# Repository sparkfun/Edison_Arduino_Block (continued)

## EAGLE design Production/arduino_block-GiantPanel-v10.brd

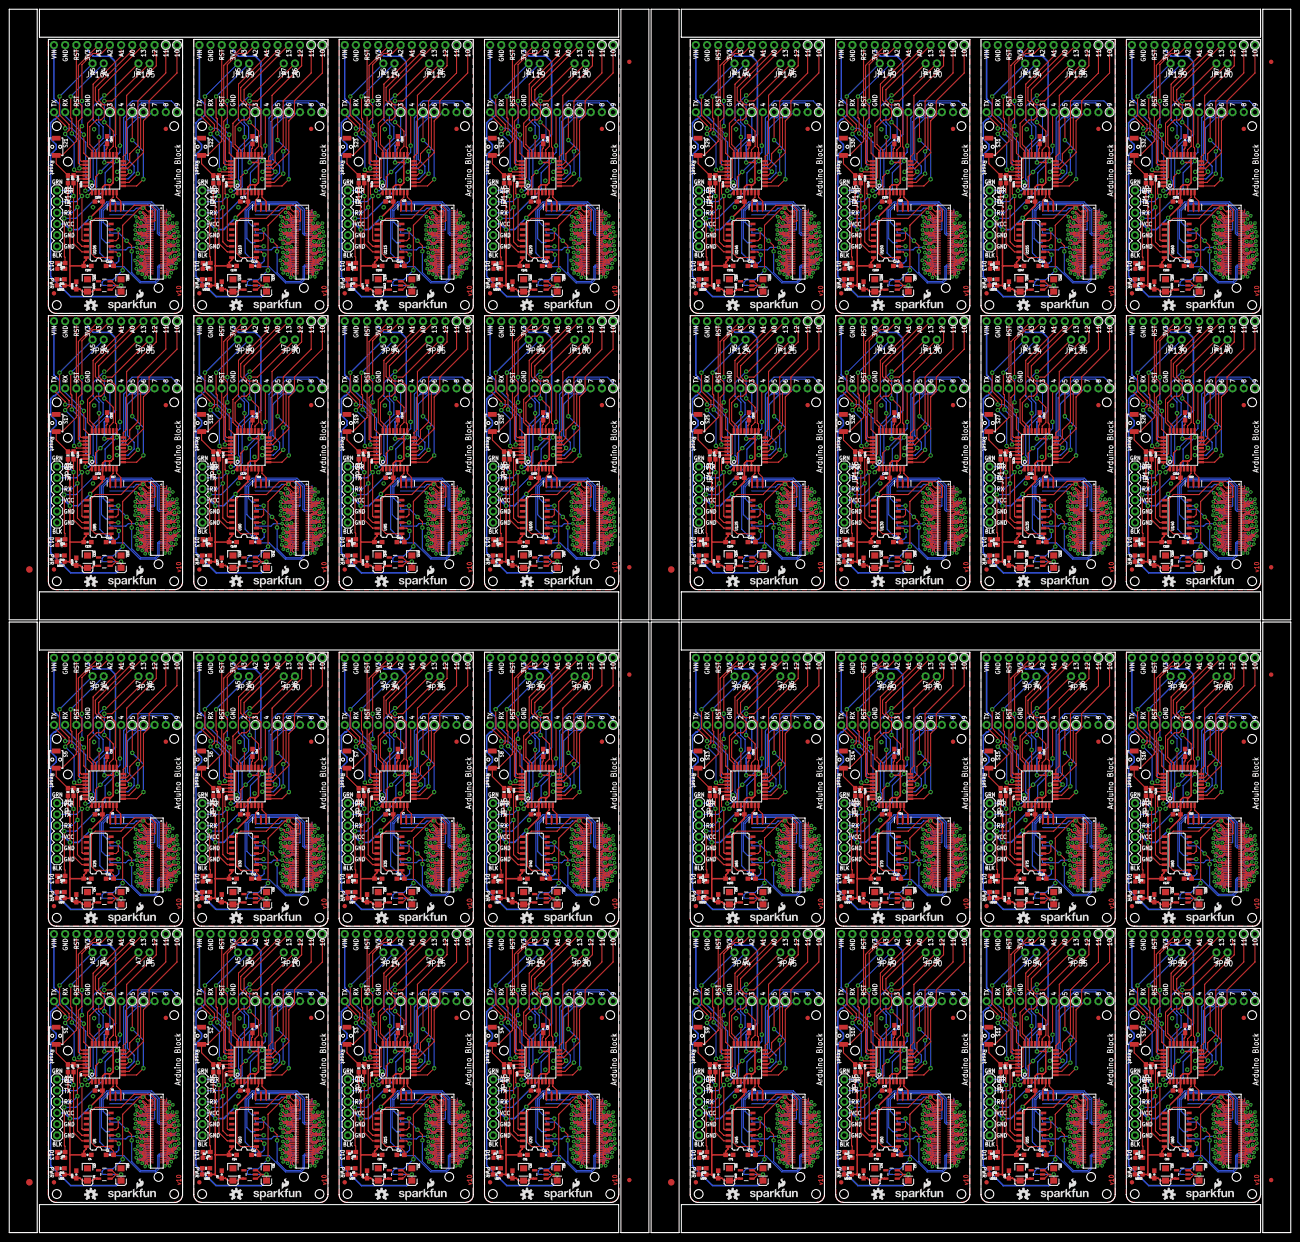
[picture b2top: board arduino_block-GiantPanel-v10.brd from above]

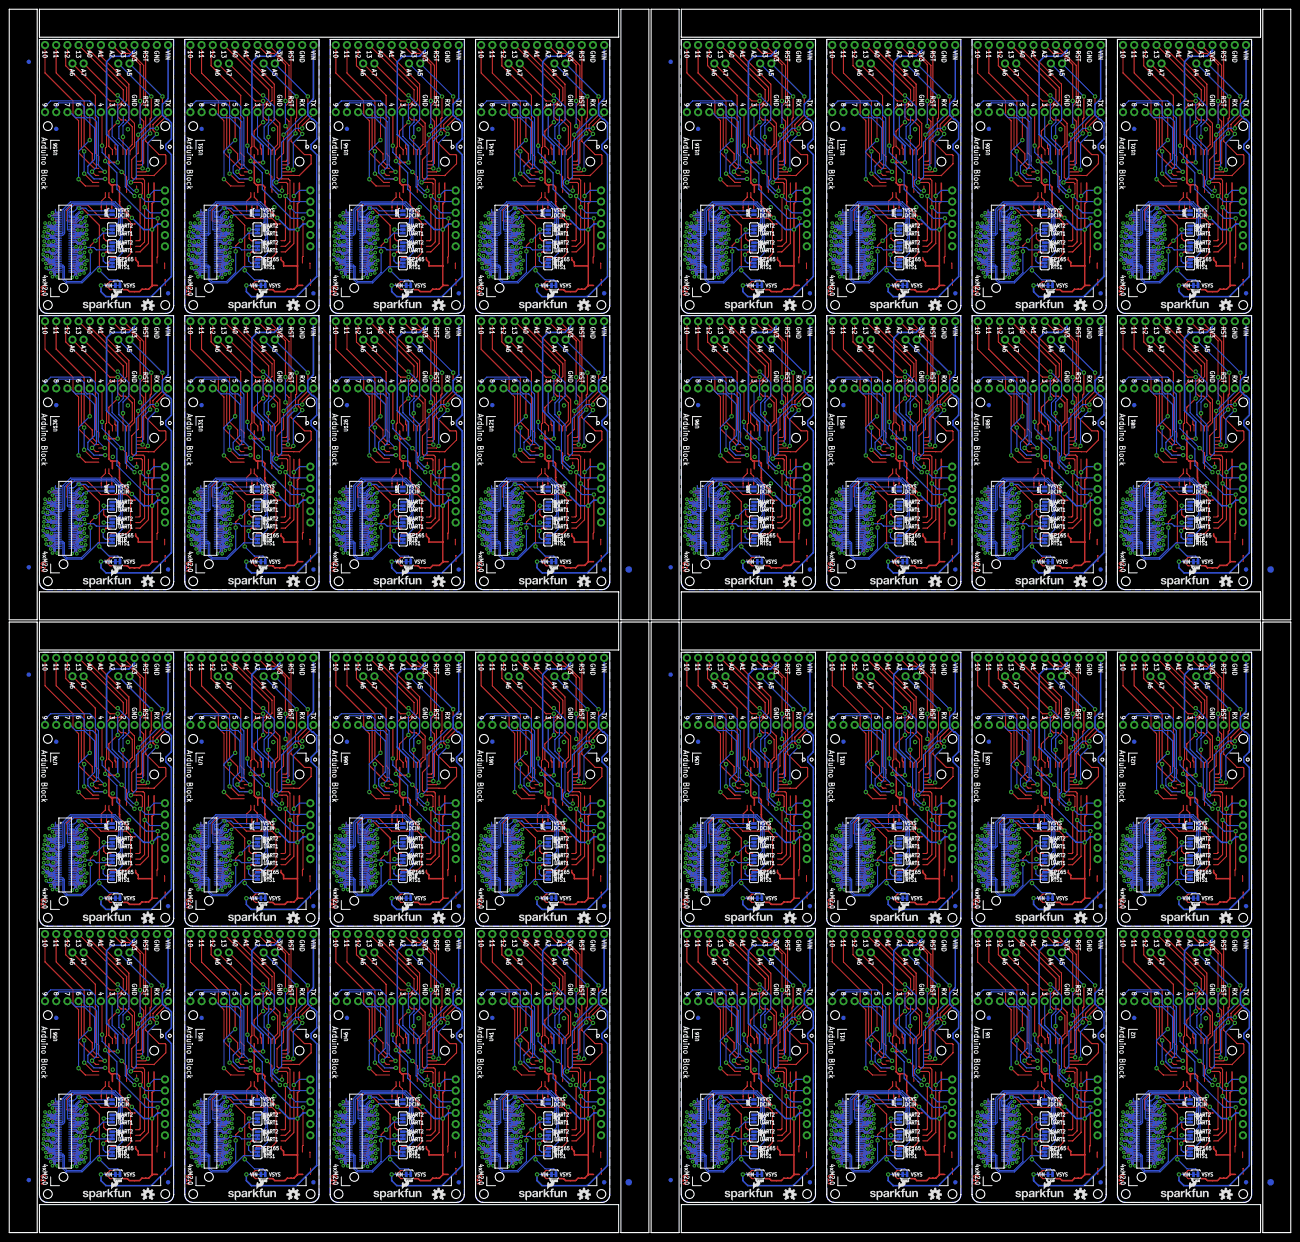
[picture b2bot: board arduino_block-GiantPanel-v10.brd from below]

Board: 2 copper layers, 291.1 x 277.9 mm, 1240 parts (364 on the bottom side), 2944 nets.

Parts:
C1, C2, C3, C4, C5, C6, C8, C9, C10, C12, C14, C15, C16, C18, C20, C22, C23, C24, C25, C27, C28, C30, C31, C32, C33, C35, C36, C38, C39, C40, C41, C43, C44, C46, C47, C48, C49, C51, C52, C54, C55, C56, C57, C59, C60, C62, C63, C64, C65, C67, C68, C70, C71, C72, C73, C75, C76, C78, C79, C80, C81, C83, C84, C86, C87, C88, C89, C91, C92, C94, C95, C96, C97, C99, C100, C102, C103, C104, C105, C107, C108, C110, C111, C112, C113, C115, C116, C118, C119, C120, C121, C123, C124, C126, C127, C128, C129, C131, C132, C134, C135, C136, C137, C139, C140, C142, C143, C144, C145, C147, C148, C150, C151, C152, C153, C155, C156, C158, C159, C160, C161, C163, C164, C166, C167, C168, C169, C171, C172, C174, C175, C176, C177, C179, C180, C182, C183, C184, C185, C187, C188, C190, C191, C192, C193, C195, C196, C198, C199, C200, C201, C203, C204, C206, C207, C208, C209, C211, C212, C214, C215, C216, C217, C219, C220, C222, C223, C224, C225, C227, C228, C230, C231, C232, C233, C235, C236, C238, C239, C240, C241, C243, C244, C246, C247, C248, C249, C251, C252, C254, C255, C256: 0.1uF; 0603-CAP
C7, C11, C13, C17, C19, C21, C26, C29, C34, C37, C42, C45, C50, C53, C58, C61, C66, C69, C74, C77, C82, C85, C90, C93, C98, C101, C106, C109, C114, C117, C122, C125, C130, C133, C138, C141, C146, C149, C154, C157, C162, C165, C170, C173, C178, C181, C186, C189, C194, C197, C202, C205, C210, C213, C218, C221, C226, C229, C234, C237, C242, C245, C250, C253: 10uF; EIA3216
D1, D2, D3, D4, D5, D6, D7, D8, D9, D10, D11, D12, D13, D14, D15, D16, D17, D18, D19, D20, D21, D22, D23, D24, D25, D26, D27, D28, D29, D30, D31, D32: Green; 0603-LED-ALT1
E$1, E$2, E$9, E$10, E$15, E$16, E$21, E$22: FIDUCIAL-1.5X3
E$3, E$4, E$5, E$6, E$7, E$8, E$11, E$12, E$13, E$14, E$17, E$18, E$19, E$20, E$23, E$24: FIDUCIAL-1X2
FID1, FID2, FID3, FID4, FID5, FID6, FID7, FID8, FID9, FID10, FID11, FID12, FID13, FID14, FID15, FID16, FID17, FID18, FID19, FID20, FID21, FID22, FID23, FID24, FID25, FID26, FID27, FID28, FID29, FID30, FID31, FID32, FID33, FID34, FID35, FID36, FID37, FID38, FID39, FID40, FID41, FID42, FID43, FID44, FID45, FID46, FID47, FID48, FID49, FID50, FID51, FID52, FID53, FID54, FID55, FID56, FID57, FID58, FID59, FID60, FID61, FID62, FID63, FID64, FID65, FID66, FID67, FID68, FID69, FID70, FID71, FID72, FID73, FID74, FID75, FID76, FID77, FID78, FID79, FID80, FID81, FID82, FID83, FID84, FID85, FID86, FID87, FID88, FID89, FID90, FID91, FID92, FID93, FID94, FID95, FID96, FID97, FID98, FID99, FID100, FID101, FID102, FID103, FID104, FID105, FID106, FID107, FID108, FID109, FID110, FID111, FID112, FID113, FID114, FID115, FID116, FID117, FID118, FID119, FID120, FID121, FID122, FID123, FID124, FID125, FID126, FID127, FID128: FIDUCIAL1X2; FIDUCIAL-1X2
JP1, JP6, JP11, JP16, JP21, JP26, JP31, JP36, JP41, JP46, JP51, JP56, JP61, JP66, JP71, JP76, JP81, JP86, JP91, JP96, JP101, JP106, JP111, JP116, JP121, JP126, JP131, JP136, JP141, JP146, JP151, JP156: FTDI Basic; 1X06
JP2, JP3, JP7, JP8, JP12, JP13, JP17, JP18, JP22, JP23, JP27, JP28, JP32, JP33, JP37, JP38, JP42, JP43, JP47, JP48, JP52, JP53, JP57, JP58, JP62, JP63, JP67, JP68, JP72, JP73, JP77, JP78, JP82, JP83, JP87, JP88, JP92, JP93, JP97, JP98, JP102, JP103, JP107, JP108, JP112, JP113, JP117, JP118, JP122, JP123, JP127, JP128, JP132, JP133, JP137, JP138, JP142, JP143, JP147, JP148, JP152, JP153, JP157, JP158: M12NO_SILK; 1X12_NO_SILK
JP4, JP5, JP9, JP10, JP14, JP15, JP19, JP20, JP24, JP25, JP29, JP30, JP34, JP35, JP39, JP40, JP44, JP45, JP49, JP50, JP54, JP55, JP59, JP60, JP64, JP65, JP69, JP70, JP74, JP75, JP79, JP80, JP84, JP85, JP89, JP90, JP94, JP95, JP99, JP100, JP104, JP105, JP109, JP110, JP114, JP115, JP119, JP120, JP124, JP125, JP129, JP130, JP134, JP135, JP139, JP140, JP144, JP145, JP149, JP150, JP154, JP155, JP159, JP160: M021X02_NO_SILK; 1X02_NO_SILK
LED1, LED2, LED3, LED4, LED5, LED6, LED7, LED8, LED9, LED10, LED11, LED12, LED13, LED14, LED15, LED16, LED17, LED18, LED19, LED20, LED21, LED22, LED23, LED24, LED25, LED26, LED27, LED28, LED29, LED30, LED31, LED32: Red; 0603-LED-ALT1
LOGO1, LOGO2, LOGO5, LOGO7, LOGO9, LOGO11, LOGO13, LOGO15, LOGO17, LOGO19, LOGO21, LOGO23, LOGO25, LOGO27, LOGO29, LOGO31, LOGO33, LOGO35, LOGO37, LOGO39, LOGO41, LOGO43, LOGO45, LOGO47, LOGO49, LOGO51, LOGO53, LOGO55, LOGO57, LOGO59, LOGO61, LOGO63, LOGO65, LOGO67, LOGO69, LOGO71, LOGO73, LOGO75, LOGO77, LOGO79, LOGO81, LOGO83, LOGO85, LOGO87, LOGO89, LOGO91, LOGO93, LOGO95, LOGO97, LOGO99, LOGO101, LOGO103, LOGO105, LOGO107, LOGO109, LOGO111, LOGO113, LOGO115, LOGO117, LOGO119, LOGO121, LOGO123, LOGO125, LOGO127: OSHW-LOGOS; OSHW-LOGO-S
LOGO3, LOGO4, LOGO6, LOGO8, LOGO10, LOGO12, LOGO14, LOGO16, LOGO18, LOGO20, LOGO22, LOGO24, LOGO26, LOGO28, LOGO30, LOGO32, LOGO34, LOGO36, LOGO38, LOGO40, LOGO42, LOGO44, LOGO46, LOGO48, LOGO50, LOGO52, LOGO54, LOGO56, LOGO58, LOGO60, LOGO62, LOGO64, LOGO66, LOGO68, LOGO70, LOGO72, LOGO74, LOGO76, LOGO78, LOGO80, LOGO82, LOGO84, LOGO86, LOGO88, LOGO90, LOGO92, LOGO94, LOGO96, LOGO98, LOGO100, LOGO102, LOGO104, LOGO106, LOGO108, LOGO110, LOGO112, LOGO114, LOGO116, LOGO118, LOGO120, LOGO122, LOGO124, LOGO126, LOGO128: SFE_LOGO_NAME_FLAME.1_INCH; SFE_LOGO_NAME_FLAME_.1
R1, R2, R3, R5, R7, R9, R10, R11, R13, R14, R16, R17, R19, R20, R22, R23, R25, R26, R28, R29, R31, R32, R34, R35, R37, R38, R40, R41, R43, R44, R46, R47, R49, R50, R52, R53, R55, R56, R58, R59, R61, R62, R64, R65, R67, R68, R70, R71, R73, R74, R76, R77, R79, R80, R82, R83, R85, R86, R88, R89, R91, R92, R94, R95: 10K; 0603-RES
R4, R6, R8, R12, R15, R18, R21, R24, R27, R30, R33, R36, R39, R42, R45, R48, R51, R54, R57, R60, R63, R66, R69, R72, R75, R78, R81, R84, R87, R90, R93, R96: 330; 0603-RES
S1, S2, S3, S4, S5, S6, S7, S8, S9, S10, S11, S12, S13, S14, S15, S16, S17, S18, S19, S20, S21, S22, S23, S24, S25, S26, S27, S28, S29, S30, S31, S32: RESET; TACTILE_SWITCH-SMD-RIGHT-ANGLE
SJ1, SJ3, SJ6, SJ9, SJ11, SJ14, SJ16, SJ19, SJ21, SJ24, SJ26, SJ29, SJ31, SJ34, SJ36, SJ39, SJ41, SJ44, SJ46, SJ49, SJ51, SJ54, SJ56, SJ59, SJ61, SJ64, SJ66, SJ69, SJ71, SJ74, SJ76, SJ79, SJ81, SJ84, SJ86, SJ89, SJ91, SJ94, SJ96, SJ99, SJ101, SJ104, SJ106, SJ109, SJ111, SJ114, SJ116, SJ119, SJ121, SJ124, SJ126, SJ129, SJ131, SJ134, SJ136, SJ139, SJ141, SJ144, SJ146, SJ149, SJ151, SJ154, SJ156, SJ159: TX; PAD-JUMPER-3-2OF3_NC_BY_TRACE_YES_SILK_FULL_BOX
SJ2, SJ7, SJ12, SJ17, SJ22, SJ27, SJ32, SJ37, SJ42, SJ47, SJ52, SJ57, SJ62, SJ67, SJ72, SJ77, SJ82, SJ87, SJ92, SJ97, SJ102, SJ107, SJ112, SJ117, SJ122, SJ127, SJ132, SJ137, SJ142, SJ147, SJ152, SJ157: RX; PAD-JUMPER-3-2OF3_NC_BY_TRACE_YES_SILK_FULL_BOX
SJ4, SJ8, SJ13, SJ18, SJ23, SJ28, SJ33, SJ38, SJ43, SJ48, SJ53, SJ58, SJ63, SJ68, SJ73, SJ78, SJ83, SJ88, SJ93, SJ98, SJ103, SJ108, SJ113, SJ118, SJ123, SJ128, SJ133, SJ138, SJ143, SJ148, SJ153, SJ158: VIN; PAD-JUMPER-2-NC_BY_TRACE_YES_SILK
SJ5, SJ10, SJ15, SJ20, SJ25, SJ30, SJ35, SJ40, SJ45, SJ50, SJ55, SJ60, SJ65, SJ70, SJ75, SJ80, SJ85, SJ90, SJ95, SJ100, SJ105, SJ110, SJ115, SJ120, SJ125, SJ130, SJ135, SJ140, SJ145, SJ150, SJ155, SJ160: DCIN; PAD-JUMPER-2-NO_YES_SILK
U1, U8, U13, U18, U23, U28, U33, U38, U43, U48, U53, U58, U63, U68, U73, U78, U83, U88, U93, U98, U103, U108, U113, U118, U123, U128, U133, U138, U143, U148, U153, U158: MIC5205-3.3V (150mA); SOT23-5
U2, U6, U11, U16, U21, U26, U31, U36, U41, U46, U51, U56, U61, U66, U71, U76, U81, U86, U91, U96, U101, U106, U111, U116, U121, U126, U131, U136, U141, U146, U151, U156: EDISON_CONNECTOR_FULLMOUNTING_HOLES; EDISON_DAUGHTER
U3, U7, U12, U17, U22, U27, U32, U37, U42, U47, U52, U57, U62, U67, U72, U77, U82, U87, U92, U97, U102, U107, U112, U117, U122, U127, U132, U137, U142, U147, U152, U157: EDISON_CONNECTOR_FULLHEADER; DF40C-70DP-0.4(51)
U4, U9, U14, U19, U24, U29, U34, U39, U44, U49, U54, U59, U64, U69, U74, U79, U84, U89, U94, U99, U104, U109, U114, U119, U124, U129, U134, U139, U144, U149, U154, U159: ATMEGA328; TQFP32-08
U5, U10, U15, U20, U25, U30, U35, U40, U45, U50, U55, U60, U65, U70, U75, U80, U85, U90, U95, U100, U105, U110, U115, U120, U125, U130, U135, U140, U145, U150, U155, U160: SO14
Y1, Y2, Y3, Y4, Y5, Y6, Y7, Y8, Y9, Y10, Y11, Y12, Y13, Y14, Y15, Y16, Y17, Y18, Y19, Y20, Y21, Y22, Y23, Y24, Y25, Y26, Y27, Y28, Y29, Y30, Y31, Y32: 8MHZ; RESONATOR-SMD

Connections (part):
1.8V: C5.2, U2.12, U3.12, U5.1, U5.8
1.8V1: C15.2, U6.12, U7.12, U10.1, U10.8
1.8V2: C24.2, U11.12, U12.12, U15.1, U15.8
1.8V3: C32.2, U16.12, U17.12, U20.1, U20.8
1.8V4: C40.2, U21.12, U22.12, U25.1, U25.8
1.8V5: C48.2, U26.12, U27.12, U30.1, U30.8
1.8V6: C56.2, U31.12, U32.12, U35.1, U35.8
1.8V7: C64.2, U36.12, U37.12, U40.1, U40.8
1.8V8: C72.2, U41.12, U42.12, U45.1, U45.8
1.8V9: C80.2, U46.12, U47.12, U50.1, U50.8
1.8V10: C88.2, U51.12, U52.12, U55.1, U55.8
1.8V11: C96.2, U56.12, U57.12, U60.1, U60.8
1.8V12: C104.2, U61.12, U62.12, U65.1, U65.8
1.8V13: C112.2, U66.12, U67.12, U70.1, U70.8
1.8V14: C120.2, U71.12, U72.12, U75.1, U75.8
1.8V15: C128.2, U76.12, U77.12, U80.1, U80.8
1.8V16: C136.2, U81.12, U82.12, U85.1, U85.8
1.8V17: C144.2, U86.12, U87.12, U90.1, U90.8
1.8V18: C152.2, U91.12, U92.12, U95.1, U95.8
1.8V19: C160.2, U96.12, U97.12, U100.1, U100.8
1.8V20: C168.2, U101.12, U102.12, U105.1, U105.8
1.8V21: C176.2, U106.12, U107.12, U110.1, U110.8
1.8V22: C184.2, U111.12, U112.12, U115.1, U115.8
1.8V23: C192.2, U116.12, U117.12, U120.1, U120.8
1.8V24: C200.2, U121.12, U122.12, U125.1, U125.8
1.8V25: C208.2, U126.12, U127.12, U130.1, U130.8
1.8V26: C216.2, U131.12, U132.12, U135.1, U135.8
1.8V27: C224.2, U136.12, U137.12, U140.1, U140.8
1.8V28: C232.2, U141.12, U142.12, U145.1, U145.8
1.8V29: C240.2, U146.12, U147.12, U150.1, U150.8
1.8V30: C248.2, U151.12, U152.12, U155.1, U155.8
1.8V31: C256.2, U156.12, U157.12, U160.1, U160.8
3.3V: U2.8, U2.10, U3.8, U3.10
3.3V1: U6.8, U6.10, U7.8, U7.10
3.3V2: U11.8, U11.10, U12.8, U12.10
3.3V3: U16.8, U16.10, U17.8, U17.10
3.3V4: U21.8, U21.10, U22.8, U22.10
3.3V5: U26.8, U26.10, U27.8, U27.10
3.3V6: U31.8, U31.10, U32.8, U32.10
3.3V7: U36.8, U36.10, U37.8, U37.10
3.3V8: U41.8, U41.10, U42.8, U42.10
3.3V9: U46.8, U46.10, U47.8, U47.10
3.3V10: U51.8, U51.10, U52.8, U52.10
3.3V11: U56.8, U56.10, U57.8, U57.10
3.3V12: U61.8, U61.10, U62.8, U62.10
3.3V13: U66.8, U66.10, U67.8, U67.10
3.3V14: U71.8, U71.10, U72.8, U72.10
3.3V15: U76.8, U76.10, U77.8, U77.10
3.3V16: U81.8, U81.10, U82.8, U82.10
3.3V17: U86.8, U86.10, U87.8, U87.10
3.3V18: U91.8, U91.10, U92.8, U92.10
3.3V19: U96.8, U96.10, U97.8, U97.10
3.3V20: U101.8, U101.10, U102.8, U102.10
3.3V21: U106.8, U106.10, U107.8, U107.10
3.3V22: U111.8, U111.10, U112.8, U112.10
3.3V23: U116.8, U116.10, U117.8, U117.10
3.3V24: U121.8, U121.10, U122.8, U122.10
3.3V25: U126.8, U126.10, U127.8, U127.10
3.3V26: U131.8, U131.10, U132.8, U132.10
3.3V27: U136.8, U136.10, U137.8, U137.10
3.3V28: U141.8, U141.10, U142.8, U142.10
3.3V29: U146.8, U146.10, U147.8, U147.10
3.3V30: U151.8, U151.10, U152.8, U152.10
3.3V31: U156.8, U156.10, U157.8, U157.10
A0: JP2.8, U4.23
A1: JP2.7, U4.24
A2: JP2.6, U4.25
A3: JP2.5, U4.26
A4: JP4.1, U4.27
A5: JP4.2, U4.28
A6: JP5.1, U4.19
A7: JP5.2, U4.22
A8: JP9.2, U9.28
A9: JP9.1, U9.27
A10: JP7.5, U9.26
A11: JP7.6, U9.25
A12: JP7.7, U9.24
A13: JP7.8, U9.23
A14: JP10.1, U9.19
A15: JP10.2, U9.22
A16: JP14.2, U14.28
A17: JP14.1, U14.27
A18: JP12.5, U14.26
A19: JP12.6, U14.25
A20: JP12.7, U14.24
A21: JP12.8, U14.23
A22: JP15.1, U14.19
A23: JP15.2, U14.22
A24: JP19.2, U19.28
A25: JP19.1, U19.27
A26: JP17.5, U19.26
A27: JP17.6, U19.25
A28: JP17.7, U19.24
A29: JP17.8, U19.23
A30: JP20.1, U19.19
A31: JP20.2, U19.22
A32: JP24.2, U24.28
A33: JP24.1, U24.27
A34: JP22.5, U24.26
A35: JP22.6, U24.25
A36: JP22.7, U24.24
A37: JP22.8, U24.23
A38: JP25.1, U24.19
A39: JP25.2, U24.22
A40: JP29.2, U29.28
A41: JP29.1, U29.27
A42: JP27.5, U29.26
A43: JP27.6, U29.25
A44: JP27.7, U29.24
A45: JP27.8, U29.23
A46: JP30.1, U29.19
A47: JP30.2, U29.22
A48: JP34.2, U34.28
A49: JP34.1, U34.27
A50: JP32.5, U34.26
A51: JP32.6, U34.25
A52: JP32.7, U34.24
A53: JP32.8, U34.23
A54: JP35.1, U34.19
A55: JP35.2, U34.22
A56: JP39.2, U39.28
A57: JP39.1, U39.27
A58: JP37.5, U39.26
A59: JP37.6, U39.25
A60: JP37.7, U39.24
A61: JP37.8, U39.23
A62: JP40.1, U39.19
A63: JP40.2, U39.22
A64: JP44.2, U44.28
A65: JP44.1, U44.27
A66: JP42.5, U44.26
A67: JP42.6, U44.25
A68: JP42.7, U44.24
A69: JP42.8, U44.23
A70: JP45.1, U44.19
A71: JP45.2, U44.22
A72: JP49.2, U49.28
A73: JP49.1, U49.27
A74: JP47.5, U49.26
A75: JP47.6, U49.25
A76: JP47.7, U49.24
A77: JP47.8, U49.23
A78: JP50.1, U49.19
A79: JP50.2, U49.22
A80: JP54.2, U54.28
A81: JP54.1, U54.27
A82: JP52.5, U54.26
A83: JP52.6, U54.25
A84: JP52.7, U54.24
A85: JP52.8, U54.23
A86: JP55.1, U54.19
A87: JP55.2, U54.22
A88: JP59.2, U59.28
A89: JP59.1, U59.27
A90: JP57.5, U59.26
A91: JP57.6, U59.25
A92: JP57.7, U59.24
A93: JP57.8, U59.23
A94: JP60.1, U59.19
A95: JP60.2, U59.22
A96: JP64.2, U64.28
A97: JP64.1, U64.27
A98: JP62.5, U64.26
A99: JP62.6, U64.25
A100: JP62.7, U64.24
A101: JP62.8, U64.23
A102: JP65.1, U64.19
A103: JP65.2, U64.22
A104: JP69.2, U69.28
A105: JP69.1, U69.27
A106: JP67.5, U69.26
A107: JP67.6, U69.25
A108: JP67.7, U69.24
A109: JP67.8, U69.23
A110: JP70.1, U69.19
A111: JP70.2, U69.22
A112: JP74.2, U74.28
A113: JP74.1, U74.27
A114: JP72.5, U74.26
A115: JP72.6, U74.25
A116: JP72.7, U74.24
A117: JP72.8, U74.23
A118: JP75.1, U74.19
A119: JP75.2, U74.22
A120: JP79.2, U79.28
A121: JP79.1, U79.27
A122: JP77.5, U79.26
A123: JP77.6, U79.25
A124: JP77.7, U79.24
A125: JP77.8, U79.23
A126: JP80.1, U79.19
A127: JP80.2, U79.22
A128: JP84.2, U84.28
A129: JP84.1, U84.27
A130: JP82.5, U84.26
A131: JP82.6, U84.25
A132: JP82.7, U84.24
A133: JP82.8, U84.23
A134: JP85.1, U84.19
A135: JP85.2, U84.22
A136: JP89.2, U89.28
A137: JP89.1, U89.27
A138: JP87.5, U89.26
A139: JP87.6, U89.25
A140: JP87.7, U89.24
A141: JP87.8, U89.23
A142: JP90.1, U89.19
A143: JP90.2, U89.22
A144: JP94.2, U94.28
A145: JP94.1, U94.27
A146: JP92.5, U94.26
A147: JP92.6, U94.25
A148: JP92.7, U94.24
A149: JP92.8, U94.23
A150: JP95.1, U94.19
A151: JP95.2, U94.22
A152: JP99.2, U99.28
A153: JP99.1, U99.27
A154: JP97.5, U99.26
A155: JP97.6, U99.25
A156: JP97.7, U99.24
A157: JP97.8, U99.23
A158: JP100.1, U99.19
A159: JP100.2, U99.22
A160: JP104.2, U104.28
A161: JP104.1, U104.27
A162: JP102.5, U104.26
A163: JP102.6, U104.25
A164: JP102.7, U104.24
A165: JP102.8, U104.23
A166: JP105.1, U104.19
A167: JP105.2, U104.22
A168: JP109.2, U109.28
A169: JP109.1, U109.27
A170: JP107.5, U109.26
A171: JP107.6, U109.25
A172: JP107.7, U109.24
A173: JP107.8, U109.23
A174: JP110.1, U109.19
A175: JP110.2, U109.22
A176: JP114.2, U114.28
A177: JP114.1, U114.27
A178: JP112.5, U114.26
A179: JP112.6, U114.25
A180: JP112.7, U114.24
A181: JP112.8, U114.23
A182: JP115.1, U114.19
A183: JP115.2, U114.22
A184: JP119.2, U119.28
A185: JP119.1, U119.27
A186: JP117.5, U119.26
A187: JP117.6, U119.25
A188: JP117.7, U119.24
A189: JP117.8, U119.23
A190: JP120.1, U119.19
A191: JP120.2, U119.22
A192: JP124.2, U124.28
A193: JP124.1, U124.27
A194: JP122.5, U124.26
A195: JP122.6, U124.25
A196: JP122.7, U124.24
A197: JP122.8, U124.23
A198: JP125.1, U124.19
A199: JP125.2, U124.22
A200: JP129.2, U129.28
A201: JP129.1, U129.27
A202: JP127.5, U129.26
A203: JP127.6, U129.25
A204: JP127.7, U129.24
A205: JP127.8, U129.23
A206: JP130.1, U129.19
A207: JP130.2, U129.22
A208: JP134.2, U134.28
A209: JP134.1, U134.27
A210: JP132.5, U134.26
A211: JP132.6, U134.25
A212: JP132.7, U134.24
A213: JP132.8, U134.23
A214: JP135.1, U134.19
A215: JP135.2, U134.22
A216: JP139.2, U139.28
A217: JP139.1, U139.27
A218: JP137.5, U139.26
A219: JP137.6, U139.25
A220: JP137.7, U139.24
A221: JP137.8, U139.23
A222: JP140.1, U139.19
A223: JP140.2, U139.22
A224: JP144.2, U144.28
A225: JP144.1, U144.27
A226: JP142.5, U144.26
A227: JP142.6, U144.25
A228: JP142.7, U144.24
A229: JP142.8, U144.23
A230: JP145.1, U144.19
A231: JP145.2, U144.22
A232: JP149.2, U149.28
A233: JP149.1, U149.27
A234: JP147.5, U149.26
A235: JP147.6, U149.25
A236: JP147.7, U149.24
A237: JP147.8, U149.23
A238: JP150.1, U149.19
A239: JP150.2, U149.22
A240: JP154.2, U154.28
A241: JP154.1, U154.27
A242: JP152.5, U154.26
A243: JP152.6, U154.25
A244: JP152.7, U154.24
A245: JP152.8, U154.23
A246: JP155.1, U154.19
A247: JP155.2, U154.22
A248: JP159.2, U159.28
A249: JP159.1, U159.27
A250: JP157.5, U159.26
A251: JP157.6, U159.25
A252: JP157.7, U159.24
A253: JP157.8, U159.23
A254: JP160.1, U159.19
A255: JP160.2, U159.22
ARD_DTR: C2.2, JP1.1, U5.13
ARD_DTR1: C12.2, JP6.1, U10.13
ARD_DTR2: C22.2, JP11.1, U15.13
ARD_DTR3: C30.2, JP16.1, U20.13
ARD_DTR4: C38.2, JP21.1, U25.13
ARD_DTR5: C46.2, JP26.1, U30.13
ARD_DTR6: C54.2, JP31.1, U35.13
ARD_DTR7: C62.2, JP36.1, U40.13
ARD_DTR8: C70.2, JP41.1, U45.13
ARD_DTR9: C78.2, JP46.1, U50.13
ARD_DTR10: C86.2, JP51.1, U55.13
ARD_DTR11: C94.2, JP56.1, U60.13
ARD_DTR12: C102.2, JP61.1, U65.13
ARD_DTR13: C110.2, JP66.1, U70.13
ARD_DTR14: C118.2, JP71.1, U75.13
ARD_DTR15: C126.2, JP76.1, U80.13
ARD_DTR16: C134.2, JP81.1, U85.13
ARD_DTR17: C142.2, JP86.1, U90.13
ARD_DTR18: C150.2, JP91.1, U95.13
ARD_DTR19: C158.2, JP96.1, U100.13
ARD_DTR20: C166.2, JP101.1, U105.13
ARD_DTR21: C174.2, JP106.1, U110.13
ARD_DTR22: C182.2, JP111.1, U115.13
ARD_DTR23: C190.2, JP116.1, U120.13
ARD_DTR24: C198.2, JP121.1, U125.13
ARD_DTR25: C206.2, JP126.1, U130.13
ARD_DTR26: C214.2, JP131.1, U135.13
ARD_DTR27: C222.2, JP136.1, U140.13
ARD_DTR28: C230.2, JP141.1, U145.13
ARD_DTR29: C238.2, JP146.1, U150.13
ARD_DTR30: C246.2, JP151.1, U155.13
ARD_DTR31: C254.2, JP156.1, U160.13
ARD_RX: JP1.3, JP3.2, U4.30, U5.12
ARD_RX1: JP6.3, JP8.2, U9.30, U10.12
ARD_RX2: JP11.3, JP13.2, U14.30, U15.12
ARD_RX3: JP16.3, JP18.2, U19.30, U20.12
ARD_RX4: JP21.3, JP23.2, U24.30, U25.12
ARD_RX5: JP26.3, JP28.2, U29.30, U30.12
ARD_RX6: JP31.3, JP33.2, U34.30, U35.12
ARD_RX7: JP36.3, JP38.2, U39.30, U40.12
ARD_RX8: JP41.3, JP43.2, U44.30, U45.12
ARD_RX9: JP46.3, JP48.2, U49.30, U50.12
ARD_RX10: JP51.3, JP53.2, U54.30, U55.12
ARD_RX11: JP56.3, JP58.2, U59.30, U60.12
ARD_RX12: JP61.3, JP63.2, U64.30, U65.12
ARD_RX13: JP66.3, JP68.2, U69.30, U70.12
ARD_RX14: JP71.3, JP73.2, U74.30, U75.12
ARD_RX15: JP76.3, JP78.2, U79.30, U80.12
ARD_RX16: JP81.3, JP83.2, U84.30, U85.12
ARD_RX17: JP86.3, JP88.2, U89.30, U90.12
ARD_RX18: JP91.3, JP93.2, U94.30, U95.12
ARD_RX19: JP96.3, JP98.2, U99.30, U100.12
ARD_RX20: JP101.3, JP103.2, U104.30, U105.12
ARD_RX21: JP106.3, JP108.2, U109.30, U110.12
ARD_RX22: JP111.3, JP113.2, U114.30, U115.12
ARD_RX23: JP116.3, JP118.2, U119.30, U120.12
ARD_RX24: JP121.3, JP123.2, U124.30, U125.12
ARD_RX25: JP126.3, JP128.2, U129.30, U130.12
ARD_RX26: JP131.3, JP133.2, U134.30, U135.12
ARD_RX27: JP136.3, JP138.2, U139.30, U140.12
ARD_RX28: JP141.3, JP143.2, U144.30, U145.12
ARD_RX29: JP146.3, JP148.2, U149.30, U150.12
ARD_RX30: JP151.3, JP153.2, U154.30, U155.12
ARD_RX31: JP156.3, JP158.2, U159.30, U160.12
ARD_TX: JP1.2, JP3.1, U4.31, U5.11
ARD_TX1: JP6.2, JP8.1, U9.31, U10.11
ARD_TX2: JP11.2, JP13.1, U14.31, U15.11
ARD_TX3: JP16.2, JP18.1, U19.31, U20.11
ARD_TX4: JP21.2, JP23.1, U24.31, U25.11
ARD_TX5: JP26.2, JP28.1, U29.31, U30.11
ARD_TX6: JP31.2, JP33.1, U34.31, U35.11
ARD_TX7: JP36.2, JP38.1, U39.31, U40.11
ARD_TX8: JP41.2, JP43.1, U44.31, U45.11
ARD_TX9: JP46.2, JP48.1, U49.31, U50.11
ARD_TX10: JP51.2, JP53.1, U54.31, U55.11
ARD_TX11: JP56.2, JP58.1, U59.31, U60.11
ARD_TX12: JP61.2, JP63.1, U64.31, U65.11
ARD_TX13: JP66.2, JP68.1, U69.31, U70.11
ARD_TX14: JP71.2, JP73.1, U74.31, U75.11
ARD_TX15: JP76.2, JP78.1, U79.31, U80.11
ARD_TX16: JP81.2, JP83.1, U84.31, U85.11
ARD_TX17: JP86.2, JP88.1, U89.31, U90.11
ARD_TX18: JP91.2, JP93.1, U94.31, U95.11
ARD_TX19: JP96.2, JP98.1, U99.31, U100.11
ARD_TX20: JP101.2, JP103.1, U104.31, U105.11
ARD_TX21: JP106.2, JP108.1, U109.31, U110.11
ARD_TX22: JP111.2, JP113.1, U114.31, U115.11
ARD_TX23: JP116.2, JP118.1, U119.31, U120.11
ARD_TX24: JP121.2, JP123.1, U124.31, U125.11
ARD_TX25: JP126.2, JP128.1, U129.31, U130.11
ARD_TX26: JP131.2, JP133.1, U134.31, U135.11
ARD_TX27: JP136.2, JP138.1, U139.31, U140.11
ARD_TX28: JP141.2, JP143.1, U144.31, U145.11
ARD_TX29: JP146.2, JP148.1, U149.31, U150.11
ARD_TX30: JP151.2, JP153.1, U154.31, U155.11
ARD_TX31: JP156.2, JP158.1, U159.31, U160.11
AREF: C1.2, U4.20
AREF1: C9.2, U9.20
AREF2: C20.2, U14.20
AREF3: C28.2, U19.20
AREF4: C36.2, U24.20
AREF5: C44.2, U29.20
AREF6: C52.2, U34.20
AREF7: C60.2, U39.20
AREF8: C68.2, U44.20
AREF9: C76.2, U49.20
AREF10: C84.2, U54.20
AREF11: C92.2, U59.20
AREF12: C100.2, U64.20
AREF13: C108.2, U69.20
AREF14: C116.2, U74.20
AREF15: C124.2, U79.20
AREF16: C132.2, U84.20
AREF17: C140.2, U89.20
AREF18: C148.2, U94.20
AREF19: C156.2, U99.20
AREF20: C164.2, U104.20
AREF21: C172.2, U109.20
AREF22: C180.2, U114.20
AREF23: C188.2, U119.20
AREF24: C196.2, U124.20
AREF25: C204.2, U129.20
AREF26: C212.2, U134.20
AREF27: C220.2, U139.20
AREF28: C228.2, U144.20
AREF29: C236.2, U149.20
AREF30: C244.2, U154.20
AREF31: C252.2, U159.20
D1: JP8.12, U9.13
D2: JP3.5, U4.32
D3: JP3.6, U4.1
D4: JP3.7, U4.2
D5: JP3.8, U4.9
D6: JP3.9, U4.10
D7: JP3.10, U4.11
D8: JP3.11, U4.12
D9: JP3.12, U4.13
D10: JP2.12, U4.14
D11: JP8.11, U9.12
D12: JP8.5, U9.32
D13: JP8.6, U9.1
D14: JP8.7, U9.2
D15: JP8.8, U9.9
D16: JP8.9, U9.10
D17: JP8.10, U9.11
D18: JP7.12, U9.14
D19: JP13.12, U14.13
D20: JP13.11, U14.12
D21: JP13.5, U14.32
D22: JP13.6, U14.1
D23: JP13.7, U14.2
D24: JP13.8, U14.9
D25: JP13.9, U14.10
D26: JP13.10, U14.11
D27: JP12.12, U14.14
D28: JP18.12, U19.13
D29: JP18.11, U19.12
D30: JP18.5, U19.32
D31: JP18.6, U19.1
D32: JP18.7, U19.2
D33: JP18.8, U19.9
D34: JP18.9, U19.10
D35: JP18.10, U19.11
D36: JP17.12, U19.14
D37: JP23.12, U24.13
D38: JP23.11, U24.12
D39: JP23.5, U24.32
D40: JP23.6, U24.1
D41: JP23.7, U24.2
D42: JP23.8, U24.9
D43: JP23.9, U24.10
D44: JP23.10, U24.11
D45: JP22.12, U24.14
D46: JP28.12, U29.13
D47: JP28.11, U29.12
D48: JP28.5, U29.32
D49: JP28.6, U29.1
D50: JP28.7, U29.2
D51: JP28.8, U29.9
D52: JP28.9, U29.10
D53: JP28.10, U29.11
D54: JP27.12, U29.14
D55: JP33.12, U34.13
D56: JP33.11, U34.12
D57: JP33.5, U34.32
D58: JP33.6, U34.1
D59: JP33.7, U34.2
D60: JP33.8, U34.9
D61: JP33.9, U34.10
D62: JP33.10, U34.11
D63: JP32.12, U34.14
D64: JP38.12, U39.13
D65: JP38.11, U39.12
D66: JP38.5, U39.32
D67: JP38.6, U39.1
D68: JP38.7, U39.2
D69: JP38.8, U39.9
D70: JP38.9, U39.10
D71: JP38.10, U39.11
D72: JP37.12, U39.14
D73: JP43.12, U44.13
D74: JP43.11, U44.12
D75: JP43.5, U44.32
D76: JP43.6, U44.1
D77: JP43.7, U44.2
D78: JP43.8, U44.9
D79: JP43.9, U44.10
D80: JP43.10, U44.11
D81: JP42.12, U44.14
D82: JP48.12, U49.13
D83: JP48.11, U49.12
D84: JP48.5, U49.32
D85: JP48.6, U49.1
D86: JP48.7, U49.2
D87: JP48.8, U49.9
D88: JP48.9, U49.10
D89: JP48.10, U49.11
D90: JP47.12, U49.14
D91: JP53.12, U54.13
D92: JP53.11, U54.12
D93: JP53.5, U54.32
D94: JP53.6, U54.1
D95: JP53.7, U54.2
D96: JP53.8, U54.9
D97: JP53.9, U54.10
D98: JP53.10, U54.11
D99: JP52.12, U54.14
D100: JP58.12, U59.13
D101: JP58.11, U59.12
D102: JP58.5, U59.32
D103: JP58.6, U59.1
D104: JP58.7, U59.2
D105: JP58.8, U59.9
D106: JP58.9, U59.10
D107: JP58.10, U59.11
D108: JP57.12, U59.14
D109: JP63.12, U64.13
D110: JP63.11, U64.12
D111: JP63.5, U64.32
D112: JP63.6, U64.1
D113: JP63.7, U64.2
D114: JP63.8, U64.9
D115: JP63.9, U64.10
D116: JP63.10, U64.11
D117: JP62.12, U64.14
D118: JP68.12, U69.13
D119: JP68.11, U69.12
D120: JP68.5, U69.32
D121: JP68.6, U69.1
D122: JP68.7, U69.2
D123: JP68.8, U69.9
D124: JP68.9, U69.10
D125: JP68.10, U69.11
D126: JP67.12, U69.14
D127: JP73.12, U74.13
D128: JP73.11, U74.12
D129: JP73.5, U74.32
D130: JP73.6, U74.1
D131: JP73.7, U74.2
D132: JP73.8, U74.9
D133: JP73.9, U74.10
D134: JP73.10, U74.11
D135: JP72.12, U74.14
D136: JP78.12, U79.13
D137: JP78.11, U79.12
D138: JP78.5, U79.32
D139: JP78.6, U79.1
D140: JP78.7, U79.2
D141: JP78.8, U79.9
D142: JP78.9, U79.10
D143: JP78.10, U79.11
D144: JP77.12, U79.14
D145: JP83.12, U84.13
D146: JP83.11, U84.12
D147: JP83.5, U84.32
D148: JP83.6, U84.1
D149: JP83.7, U84.2
D150: JP83.8, U84.9
D151: JP83.9, U84.10
D152: JP83.10, U84.11
D153: JP82.12, U84.14
D154: JP88.12, U89.13
D155: JP88.11, U89.12
D156: JP88.5, U89.32
D157: JP88.6, U89.1
D158: JP88.7, U89.2
D159: JP88.8, U89.9
D160: JP88.9, U89.10
D161: JP88.10, U89.11
D162: JP87.12, U89.14
D163: JP93.12, U94.13
D164: JP93.11, U94.12
D165: JP93.5, U94.32
D166: JP93.6, U94.1
D167: JP93.7, U94.2
D168: JP93.8, U94.9
D169: JP93.9, U94.10
D170: JP93.10, U94.11
D171: JP92.12, U94.14
D172: JP98.12, U99.13
D173: JP98.11, U99.12
D174: JP98.5, U99.32
D175: JP98.6, U99.1
D176: JP98.7, U99.2
D177: JP98.8, U99.9
D178: JP98.9, U99.10
D179: JP98.10, U99.11
D180: JP97.12, U99.14
D181: JP103.12, U104.13
D182: JP103.11, U104.12
D183: JP103.5, U104.32
D184: JP103.6, U104.1
D185: JP103.7, U104.2
D186: JP103.8, U104.9
D187: JP103.9, U104.10
D188: JP103.10, U104.11
D189: JP102.12, U104.14
D190: JP108.12, U109.13
D191: JP108.11, U109.12
D192: JP108.5, U109.32
D193: JP108.6, U109.1
D194: JP108.7, U109.2
D195: JP108.8, U109.9
D196: JP108.9, U109.10
D197: JP108.10, U109.11
D198: JP107.12, U109.14
D199: JP113.12, U114.13
D200: JP113.11, U114.12
D201: JP113.5, U114.32
D202: JP113.6, U114.1
D203: JP113.7, U114.2
D204: JP113.8, U114.9
D205: JP113.9, U114.10
D206: JP113.10, U114.11
D207: JP112.12, U114.14
D208: JP118.12, U119.13
D209: JP118.11, U119.12
D210: JP118.5, U119.32
D211: JP118.6, U119.1
D212: JP118.7, U119.2
D213: JP118.8, U119.9
D214: JP118.9, U119.10
D215: JP118.10, U119.11
D216: JP117.12, U119.14
D217: JP123.12, U124.13
D218: JP123.11, U124.12
D219: JP123.5, U124.32
D220: JP123.6, U124.1
D221: JP123.7, U124.2
D222: JP123.8, U124.9
D223: JP123.9, U124.10
D224: JP123.10, U124.11
D225: JP122.12, U124.14
D226: JP128.12, U129.13
D227: JP128.11, U129.12
D228: JP128.5, U129.32
D229: JP128.6, U129.1
D230: JP128.7, U129.2
D231: JP128.8, U129.9
D232: JP128.9, U129.10
D233: JP128.10, U129.11
D234: JP127.12, U129.14
D235: JP133.12, U134.13
D236: JP133.11, U134.12
D237: JP133.5, U134.32
D238: JP133.6, U134.1
D239: JP133.7, U134.2
D240: JP133.8, U134.9
D241: JP133.9, U134.10
D242: JP133.10, U134.11
D243: JP132.12, U134.14
D244: JP138.12, U139.13
D245: JP138.11, U139.12
D246: JP138.5, U139.32
D247: JP138.6, U139.1
D248: JP138.7, U139.2
D249: JP138.8, U139.9
D250: JP138.9, U139.10
D251: JP138.10, U139.11
D252: JP137.12, U139.14
D253: JP143.12, U144.13
D254: JP143.11, U144.12
D255: JP143.5, U144.32
D256: JP143.6, U144.1
D257: JP143.7, U144.2
D258: JP143.8, U144.9
D259: JP143.9, U144.10
D260: JP143.10, U144.11
D261: JP142.12, U144.14
D262: JP148.12, U149.13
D263: JP148.11, U149.12
D264: JP148.5, U149.32
D265: JP148.6, U149.1
D266: JP148.7, U149.2
D267: JP148.8, U149.9
D268: JP148.9, U149.10
D269: JP148.10, U149.11
D270: JP147.12, U149.14
D271: JP153.12, U154.13
D272: JP153.11, U154.12
D273: JP153.5, U154.32
D274: JP153.6, U154.1
D275: JP153.7, U154.2
D276: JP153.8, U154.9
D277: JP153.9, U154.10
D278: JP153.10, U154.11
D279: JP152.12, U154.14
D280: JP158.12, U159.13
D281: JP158.11, U159.12
D282: JP158.5, U159.32
D283: JP158.6, U159.1
D284: JP158.7, U159.2
D285: JP158.8, U159.9
D286: JP158.9, U159.10
D287: JP158.10, U159.11
D288: JP157.12, U159.14
DCIN: SJ5.1, U2.14, U3.14
DCIN1: SJ10.1, U6.14, U7.14
DCIN2: SJ15.1, U11.14, U12.14
DCIN3: SJ20.1, U16.14, U17.14
DCIN4: SJ25.1, U21.14, U22.14
DCIN5: SJ30.1, U26.14, U27.14
DCIN6: SJ35.1, U31.14, U32.14
DCIN7: SJ40.1, U36.14, U37.14
DCIN8: SJ45.1, U41.14, U42.14
DCIN9: SJ50.1, U46.14, U47.14
DCIN10: SJ55.1, U51.14, U52.14
DCIN11: SJ60.1, U56.14, U57.14
DCIN12: SJ65.1, U61.14, U62.14
DCIN13: SJ70.1, U66.14, U67.14
DCIN14: SJ75.1, U71.14, U72.14
DCIN15: SJ80.1, U76.14, U77.14
DCIN16: SJ85.1, U81.14, U82.14
DCIN17: SJ90.1, U86.14, U87.14
DCIN18: SJ95.1, U91.14, U92.14
DCIN19: SJ100.1, U96.14, U97.14
DCIN20: SJ105.1, U101.14, U102.14
DCIN21: SJ110.1, U106.14, U107.14
DCIN22: SJ115.1, U111.14, U112.14
DCIN23: SJ120.1, U116.14, U117.14
DCIN24: SJ125.1, U121.14, U122.14
DCIN25: SJ130.1, U126.14, U127.14
DCIN26: SJ135.1, U131.14, U132.14
DCIN27: SJ140.1, U136.14, U137.14
DCIN28: SJ145.1, U141.14, U142.14
DCIN29: SJ150.1, U146.14, U147.14
DCIN30: SJ155.1, U151.14, U152.14
DCIN31: SJ160.1, U156.14, U157.14
ED_DTR: SJ3.2, U5.2
ED_DTR1: SJ9.2, U10.2
ED_DTR2: SJ14.2, U15.2
ED_DTR3: SJ19.2, U20.2
ED_DTR4: SJ24.2, U25.2
ED_DTR5: SJ29.2, U30.2
ED_DTR6: SJ34.2, U35.2
ED_DTR7: SJ39.2, U40.2
ED_DTR8: SJ44.2, U45.2
ED_DTR9: SJ49.2, U50.2
ED_DTR10: SJ54.2, U55.2
ED_DTR11: SJ59.2, U60.2
ED_DTR12: SJ64.2, U65.2
ED_DTR13: SJ69.2, U70.2
ED_DTR14: SJ74.2, U75.2
ED_DTR15: SJ79.2, U80.2
ED_DTR16: SJ84.2, U85.2
ED_DTR17: SJ89.2, U90.2
ED_DTR18: SJ94.2, U95.2
ED_DTR19: SJ99.2, U100.2
ED_DTR20: SJ104.2, U105.2
ED_DTR21: SJ109.2, U110.2
ED_DTR22: SJ114.2, U115.2
ED_DTR23: SJ119.2, U120.2
ED_DTR24: SJ124.2, U125.2
ED_DTR25: SJ129.2, U130.2
ED_DTR26: SJ134.2, U135.2
ED_DTR27: SJ139.2, U140.2
ED_DTR28: SJ144.2, U145.2
ED_DTR29: SJ149.2, U150.2
ED_DTR30: SJ154.2, U155.2
ED_DTR31: SJ159.2, U160.2
ED_RX: SJ2.2, U5.4
ED_RX1: SJ7.2, U10.4
ED_RX2: SJ12.2, U15.4
ED_RX3: SJ17.2, U20.4
ED_RX4: SJ22.2, U25.4
ED_RX5: SJ27.2, U30.4
ED_RX6: SJ32.2, U35.4
ED_RX7: SJ37.2, U40.4
ED_RX8: SJ42.2, U45.4
ED_RX9: SJ47.2, U50.4
ED_RX10: SJ52.2, U55.4
ED_RX11: SJ57.2, U60.4
ED_RX12: SJ62.2, U65.4
ED_RX13: SJ67.2, U70.4
ED_RX14: SJ72.2, U75.4
ED_RX15: SJ77.2, U80.4
ED_RX16: SJ82.2, U85.4
ED_RX17: SJ87.2, U90.4
ED_RX18: SJ92.2, U95.4
ED_RX19: SJ97.2, U100.4
ED_RX20: SJ102.2, U105.4
ED_RX21: SJ107.2, U110.4
ED_RX22: SJ112.2, U115.4
ED_RX23: SJ117.2, U120.4
ED_RX24: SJ122.2, U125.4
ED_RX25: SJ127.2, U130.4
ED_RX26: SJ132.2, U135.4
ED_RX27: SJ137.2, U140.4
ED_RX28: SJ142.2, U145.4
ED_RX29: SJ147.2, U150.4
ED_RX30: SJ152.2, U155.4
ED_RX31: SJ157.2, U160.4
ED_TX: SJ1.2, U5.3
ED_TX1: SJ6.2, U10.3
ED_TX2: SJ11.2, U15.3
ED_TX3: SJ16.2, U20.3
ED_TX4: SJ21.2, U25.3
ED_TX5: SJ26.2, U30.3
ED_TX6: SJ31.2, U35.3
ED_TX7: SJ36.2, U40.3
ED_TX8: SJ41.2, U45.3
ED_TX9: SJ46.2, U50.3
ED_TX10: SJ51.2, U55.3
ED_TX11: SJ56.2, U60.3
ED_TX12: SJ61.2, U65.3
ED_TX13: SJ66.2, U70.3
ED_TX14: SJ71.2, U75.3
ED_TX15: SJ76.2, U80.3
ED_TX16: SJ81.2, U85.3
ED_TX17: SJ86.2, U90.3
ED_TX18: SJ91.2, U95.3
ED_TX19: SJ96.2, U100.3
ED_TX20: SJ101.2, U105.3
ED_TX21: SJ106.2, U110.3
ED_TX22: SJ111.2, U115.3
ED_TX23: SJ116.2, U120.3
ED_TX24: SJ121.2, U125.3
ED_TX25: SJ126.2, U130.3
ED_TX26: SJ131.2, U135.3
ED_TX27: SJ136.2, U140.3
ED_TX28: SJ141.2, U145.3
ED_TX29: SJ146.2, U150.3
ED_TX30: SJ151.2, U155.3
ED_TX31: SJ156.2, U160.3
FAULT: U2.19, U3.19
FAULT1: U6.19, U7.19
FAULT2: U11.19, U12.19
FAULT3: U16.19, U17.19
FAULT4: U21.19, U22.19
FAULT5: U26.19, U27.19
FAULT6: U31.19, U32.19
FAULT7: U36.19, U37.19
FAULT8: U41.19, U42.19
FAULT9: U46.19, U47.19
FAULT10: U51.19, U52.19
FAULT11: U56.19, U57.19
FAULT12: U61.19, U62.19
FAULT13: U66.19, U67.19
FAULT14: U71.19, U72.19
FAULT15: U76.19, U77.19
FAULT16: U81.19, U82.19
FAULT17: U86.19, U87.19
FAULT18: U91.19, U92.19
FAULT19: U96.19, U97.19
FAULT20: U101.19, U102.19
FAULT21: U106.19, U107.19
FAULT22: U111.19, U112.19
FAULT23: U116.19, U117.19
FAULT24: U121.19, U122.19
FAULT25: U126.19, U127.19
FAULT26: U131.19, U132.19
FAULT27: U136.19, U137.19
FAULT28: U141.19, U142.19
FAULT29: U146.19, U147.19
FAULT30: U151.19, U152.19
FAULT31: U156.19, U157.19
FW_RCVR: U2.69, U3.69
FW_RCVR1: U6.69, U7.69
FW_RCVR2: U11.69, U12.69
FW_RCVR3: U16.69, U17.69
FW_RCVR4: U21.69, U22.69
FW_RCVR5: U26.69, U27.69
FW_RCVR6: U31.69, U32.69
FW_RCVR7: U36.69, U37.69
FW_RCVR8: U41.69, U42.69
FW_RCVR9: U46.69, U47.69
FW_RCVR10: U51.69, U52.69
FW_RCVR11: U56.69, U57.69
FW_RCVR12: U61.69, U62.69
FW_RCVR13: U66.69, U67.69
FW_RCVR14: U71.69, U72.69
FW_RCVR15: U76.69, U77.69
FW_RCVR16: U81.69, U82.69
FW_RCVR17: U86.69, U87.69
FW_RCVR18: U91.69, U92.69
FW_RCVR19: U96.69, U97.69
FW_RCVR20: U101.69, U102.69
FW_RCVR21: U106.69, U107.69
FW_RCVR22: U111.69, U112.69
FW_RCVR23: U116.69, U117.69
FW_RCVR24: U121.69, U122.69
FW_RCVR25: U126.69, U127.69
FW_RCVR26: U131.69, U132.69
FW_RCVR27: U136.69, U137.69
FW_RCVR28: U141.69, U142.69
FW_RCVR29: U146.69, U147.69
FW_RCVR30: U151.69, U152.69
FW_RCVR31: U156.69, U157.69
GND: C1.1, C3.1, C4.1, C5.1, C10.2, C13.C, C19.C, D3.C, JP1.5, JP1.6, JP2.2, JP3.4, R11.1, S1.1, U1.2, U2.1, U2.5, U2.9, U2.11, U2.13, U2.15, U3.1, U3.5, U3.9, U3.11, U3.13, U3.15, U4.3, U4.5, U4.21, U5.7, Y1.2
GND1: C6.2, C7.C, C8.1, C9.1, C11.C, C14.1, C15.1, D1.C, JP6.5, JP6.6, JP7.2, JP8.4, R1.1, S2.1, U6.1, U6.5, U6.9, U6.11, U6.13, U6.15, U7.1, U7.5, U7.9, U7.11, U7.13, U7.15, U8.2, U9.3, U9.5, U9.21, U10.7, Y2.2
GND2: C16.2, C17.C, C18.1, C20.1, C21.C, C23.1, C24.1, D2.C, JP11.5, JP11.6, JP12.2, JP13.4, R5.1, S3.1, U11.1, U11.5, U11.9, U11.11, U11.13, U11.15, U12.1, U12.5, U12.9, U12.11, U12.13, U12.15, U13.2, U14.3, U14.5, U14.21, U15.7, Y3.2
GND3: C25.2, C26.C, C27.1, C28.1, C29.C, C31.1, C32.1, D4.C, JP16.5, JP16.6, JP17.2, JP18.4, R9.1, S4.1, U16.1, U16.5, U16.9, U16.11, U16.13, U16.15, U17.1, U17.5, U17.9, U17.11, U17.13, U17.15, U18.2, U19.3, U19.5, U19.21, U20.7, Y4.2
GND4: C33.2, C34.C, C35.1, C36.1, C37.C, C39.1, C40.1, D5.C, JP21.5, JP21.6, JP22.2, JP23.4, R13.1, S5.1, U21.1, U21.5, U21.9, U21.11, U21.13, U21.15, U22.1, U22.5, U22.9, U22.11, U22.13, U22.15, U23.2, U24.3, U24.5, U24.21, U25.7, Y5.2
GND5: C41.2, C42.C, C43.1, C44.1, C45.C, C47.1, C48.1, D6.C, JP26.5, JP26.6, JP27.2, JP28.4, R16.1, S6.1, U26.1, U26.5, U26.9, U26.11, U26.13, U26.15, U27.1, U27.5, U27.9, U27.11, U27.13, U27.15, U28.2, U29.3, U29.5, U29.21, U30.7, Y6.2
GND6: C49.2, C50.C, C51.1, C52.1, C53.C, C55.1, C56.1, D7.C, JP31.5, JP31.6, JP32.2, JP33.4, R19.1, S7.1, U31.1, U31.5, U31.9, U31.11, U31.13, U31.15, U32.1, U32.5, U32.9, U32.11, U32.13, U32.15, U33.2, U34.3, U34.5, U34.21, U35.7, Y7.2
GND7: C57.2, C58.C, C59.1, C60.1, C61.C, C63.1, C64.1, D8.C, JP36.5, JP36.6, JP37.2, JP38.4, R22.1, S8.1, U36.1, U36.5, U36.9, U36.11, U36.13, U36.15, U37.1, U37.5, U37.9, U37.11, U37.13, U37.15, U38.2, U39.3, U39.5, U39.21, U40.7, Y8.2
GND8: C65.2, C66.C, C67.1, C68.1, C69.C, C71.1, C72.1, D9.C, JP41.5, JP41.6, JP42.2, JP43.4, R25.1, S9.1, U41.1, U41.5, U41.9, U41.11, U41.13, U41.15, U42.1, U42.5, U42.9, U42.11, U42.13, U42.15, U43.2, U44.3, U44.5, U44.21, U45.7, Y9.2
GND9: C73.2, C74.C, C75.1, C76.1, C77.C, C79.1, C80.1, D10.C, JP46.5, JP46.6, JP47.2, JP48.4, R28.1, S10.1, U46.1, U46.5, U46.9, U46.11, U46.13, U46.15, U47.1, U47.5, U47.9, U47.11, U47.13, U47.15, U48.2, U49.3, U49.5, U49.21, U50.7, Y10.2
GND10: C81.2, C82.C, C83.1, C84.1, C85.C, C87.1, C88.1, D11.C, JP51.5, JP51.6, JP52.2, JP53.4, R31.1, S11.1, U51.1, U51.5, U51.9, U51.11, U51.13, U51.15, U52.1, U52.5, U52.9, U52.11, U52.13, U52.15, U53.2, U54.3, U54.5, U54.21, U55.7, Y11.2
GND11: C89.2, C90.C, C91.1, C92.1, C93.C, C95.1, C96.1, D12.C, JP56.5, JP56.6, JP57.2, JP58.4, R34.1, S12.1, U56.1, U56.5, U56.9, U56.11, U56.13, U56.15, U57.1, U57.5, U57.9, U57.11, U57.13, U57.15, U58.2, U59.3, U59.5, U59.21, U60.7, Y12.2
GND12: C97.2, C98.C, C99.1, C100.1, C101.C, C103.1, C104.1, D13.C, JP61.5, JP61.6, JP62.2, JP63.4, R37.1, S13.1, U61.1, U61.5, U61.9, U61.11, U61.13, U61.15, U62.1, U62.5, U62.9, U62.11, U62.13, U62.15, U63.2, U64.3, U64.5, U64.21, U65.7, Y13.2
GND13: C105.2, C106.C, C107.1, C108.1, C109.C, C111.1, C112.1, D14.C, JP66.5, JP66.6, JP67.2, JP68.4, R40.1, S14.1, U66.1, U66.5, U66.9, U66.11, U66.13, U66.15, U67.1, U67.5, U67.9, U67.11, U67.13, U67.15, U68.2, U69.3, U69.5, U69.21, U70.7, Y14.2
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
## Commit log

2014-08-12 initial hardware commit
2014-08-12 expanding out connector, matching it to Arduino Pro
2014-08-20 updating board description in README
2014-08-29 fixing 12-pin connectors - using NO_SILK part now
2014-09-18 Rename Edison_Mezzanine_ArduinoPro.brd to arduino_block.brd
2014-09-18 Rename Edison_Mezzanine_ArduinoPro.sch to arduino_block.sch
2014-09-18 Swapping jumpers to default to UART 1. Updating silk. (v02)
2014-09-18 Stacking DCIN through. Adding jumper to potentially connect it to VSYS
2014-09-19 Replaced reset button with new RA SMD push button
2014-09-19 moved board name to lower corner of keepout.
2014-09-23 cleaned up fills
2014-09-25 file cleanup
2014-10-17 updating connector packages. Fixing silk.
2014-10-17 fixing silk directions on bottom
2014-10-17 adjusting a few traces, relocating a jumper
2014-10-17 adding grn/blk labels to FTDI
2014-10-17 Tweak pwr and gnd traces on connectors. Reds.
2014-10-17 Fixing a bit of silk placement
2014-10-17 Ready for reds. Moved some silk to be more readable along left edge of board. No known to-do items
2014-10-21 moved fid
2014-10-21 created panels
2015-02-16 Initial commit of Edison_Firmata_Client example code.
2015-04-01 Updating README and directory file names
